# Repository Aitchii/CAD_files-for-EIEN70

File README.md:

# CAD_files-for-EIEN70
CAD files for Mechatronics project EIEN70  
Contrains three different Kicad models:   
Första-projekt = LED_ring without PCB design  
LED_ring  
IR_sensor

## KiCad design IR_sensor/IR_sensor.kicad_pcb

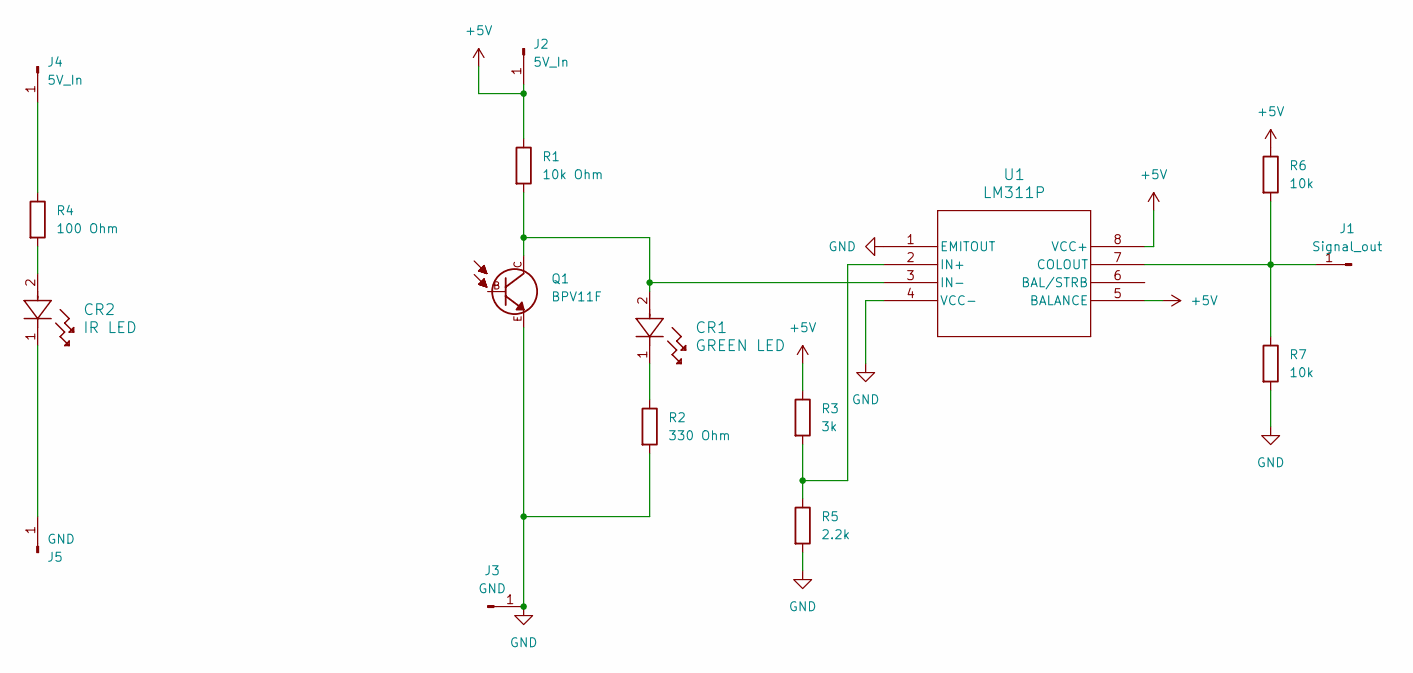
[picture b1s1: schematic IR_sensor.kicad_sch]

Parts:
CR1: GREEN LED; TLL_Series_LED_GR
CR2: IR LED; LED_D5.0mm_IRGrey
J1: Signal_out; PinHeader_1x01_P2.54mm_Vertical
J2, J4: 5V_In; PinHeader_1x01_P2.54mm_Vertical
J3, J5: GND; PinHeader_1x01_P2.54mm_Vertical
Q1: BPV11F; Phototransistor
R1: 10k Ohm; R_Axial_DIN0204_L3.6mm_D1.6mm_P5.08mm_Horizontal
R2: 330 Ohm; R_Axial_DIN0204_L3.6mm_D1.6mm_P5.08mm_Horizontal
R3: 3k; R_Axial_DIN0204_L3.6mm_D1.6mm_P5.08mm_Horizontal
R4: 100 Ohm; R_Axial_DIN0204_L3.6mm_D1.6mm_P5.08mm_Horizontal
R5: 2.2k; R_Axial_DIN0204_L3.6mm_D1.6mm_P5.08mm_Horizontal
R6, R7: 10k; R_Axial_DIN0204_L3.6mm_D1.6mm_P5.08mm_Horizontal
U1: LM311P; Voltage_comparator

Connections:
+5V: J2.1, R1.1, R3.1, R6.1, U1.5 (BALANCE), U1.8 (VCC+)
GND: J3.1, Q1.E, R2.2, R5.2, R7.2, U1.1 (EMITOUT), U1.4 (VCC-)
unnamed: CR1.1, R2.1
unnamed: CR2.2, R4.2
unnamed: J1.1, R6.2, R7.1, U1.7 (COLOUT)
unnamed: J4.1, R4.1
unnamed: CR2.1, J5.1
unnamed: R3.2, R5.1, U1.2 (IN+)
unnamed: CR1.2, Q1.C, R1.2, U1.3 (IN-)

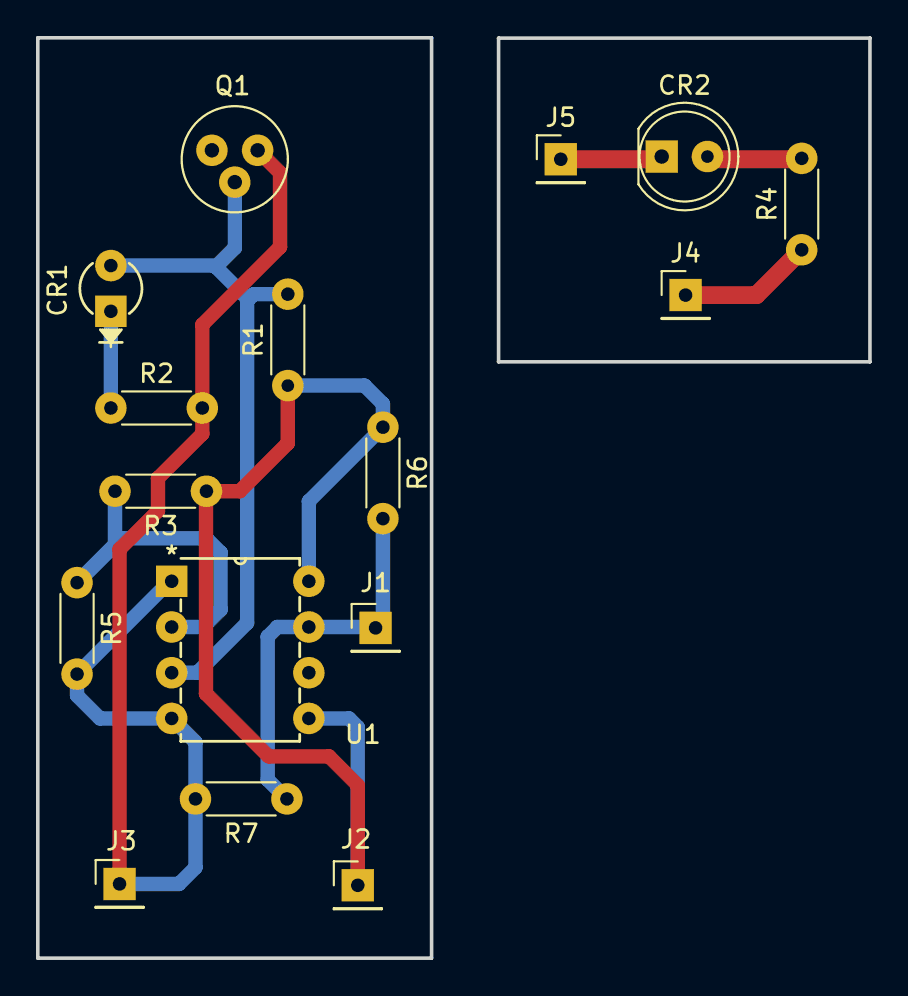
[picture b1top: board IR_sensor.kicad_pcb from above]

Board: 2 copper layers, 46.2 x 51.1 mm, 16 parts (0 on the bottom side), 9 nets.

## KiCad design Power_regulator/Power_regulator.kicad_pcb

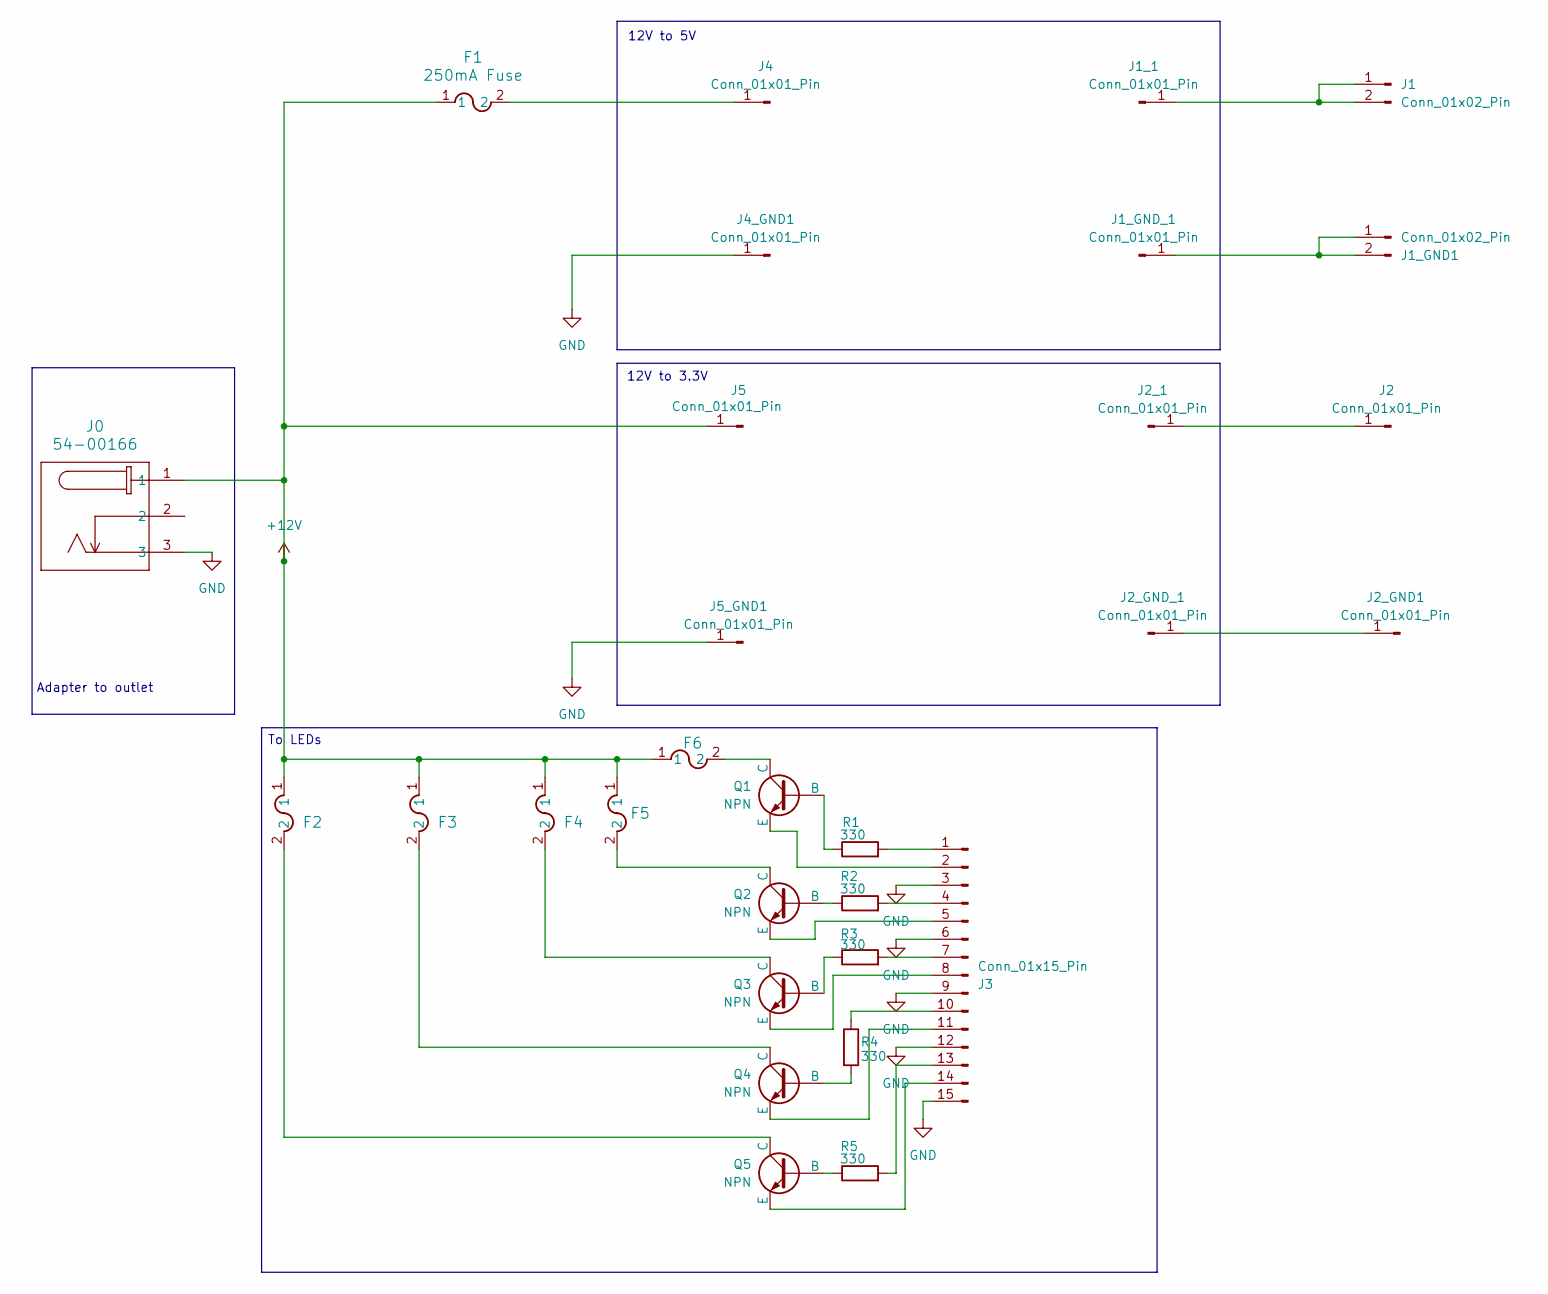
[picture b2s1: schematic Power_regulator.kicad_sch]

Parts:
F1: 250mA Fuse; FUS_LITTELFUSE_370_LTF_250mA
F2, F3, F4, F5, F6: 100mA Fuse; FUS_LITTELFUSE_396_LTF_100mA
J0: 54-00166; CONN3_54-00166_TEN
J1, J1_GND1: Conn_01x02_Pin; PinHeader_1x02_P2.54mm_Vertical
J1_1, J1_GND_1, J2, J2_1, J2_GND1, J2_GND_1, J4, J4_GND1, J5, J5_GND1: Conn_01x01_Pin; PinHeader_1x01_P2.54mm_Vertical
J3: Conn_01x15_Pin; PinHeader_1x15_P2.54mm_Vertical
Q1, Q2, Q3, Q4, Q5: NPN; NPN_transistor
R1, R2, R3, R4, R5: 330; R_Axial_DIN0204_L3.6mm_D1.6mm_P7.62mm_Horizontal

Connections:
+12V: F1.1, F2.1, F3.1, F4.1, F5.1, F6.1, J0.1, J5.1
GND: J0.3, J3.3, J3.6, J3.9, J3.12, J3.15, J4_GND1.1, J5_GND1.1
unnamed: J1.1, J1.2, J1_1.1
unnamed: J1_GND1.1, J1_GND1.2, J1_GND_1.1
unnamed: J2.1, J2_1.1
unnamed: J2_GND1.1, J2_GND_1.1
unnamed: J3.1, R1.2
unnamed: J3.2, Q1.3 (E)
unnamed: J3.4, R2.2
unnamed: J3.5, Q2.3 (E)
unnamed: J3.7, R3.2
unnamed: J3.8, Q3.3 (E)
unnamed: J3.10, R4.1
unnamed: J3.11, Q4.3 (E)
unnamed: J3.13, R5.2
unnamed: J3.14, Q5.3 (E)
unnamed: F1.2, J4.1
unnamed: Q1.2 (B), R1.1
unnamed: F6.2, Q1.1 (C)
unnamed: Q2.2 (B), R2.1
unnamed: F5.2, Q2.1 (C)
unnamed: Q3.2 (B), R3.1
unnamed: F4.2, Q3.1 (C)
unnamed: Q4.2 (B), R4.2
unnamed: F3.2, Q4.1 (C)
unnamed: Q5.2 (B), R5.1
unnamed: F2.2, Q5.1 (C)

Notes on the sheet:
To LEDs
12V to 5V
12V to 3.3V
Adapter to outlet

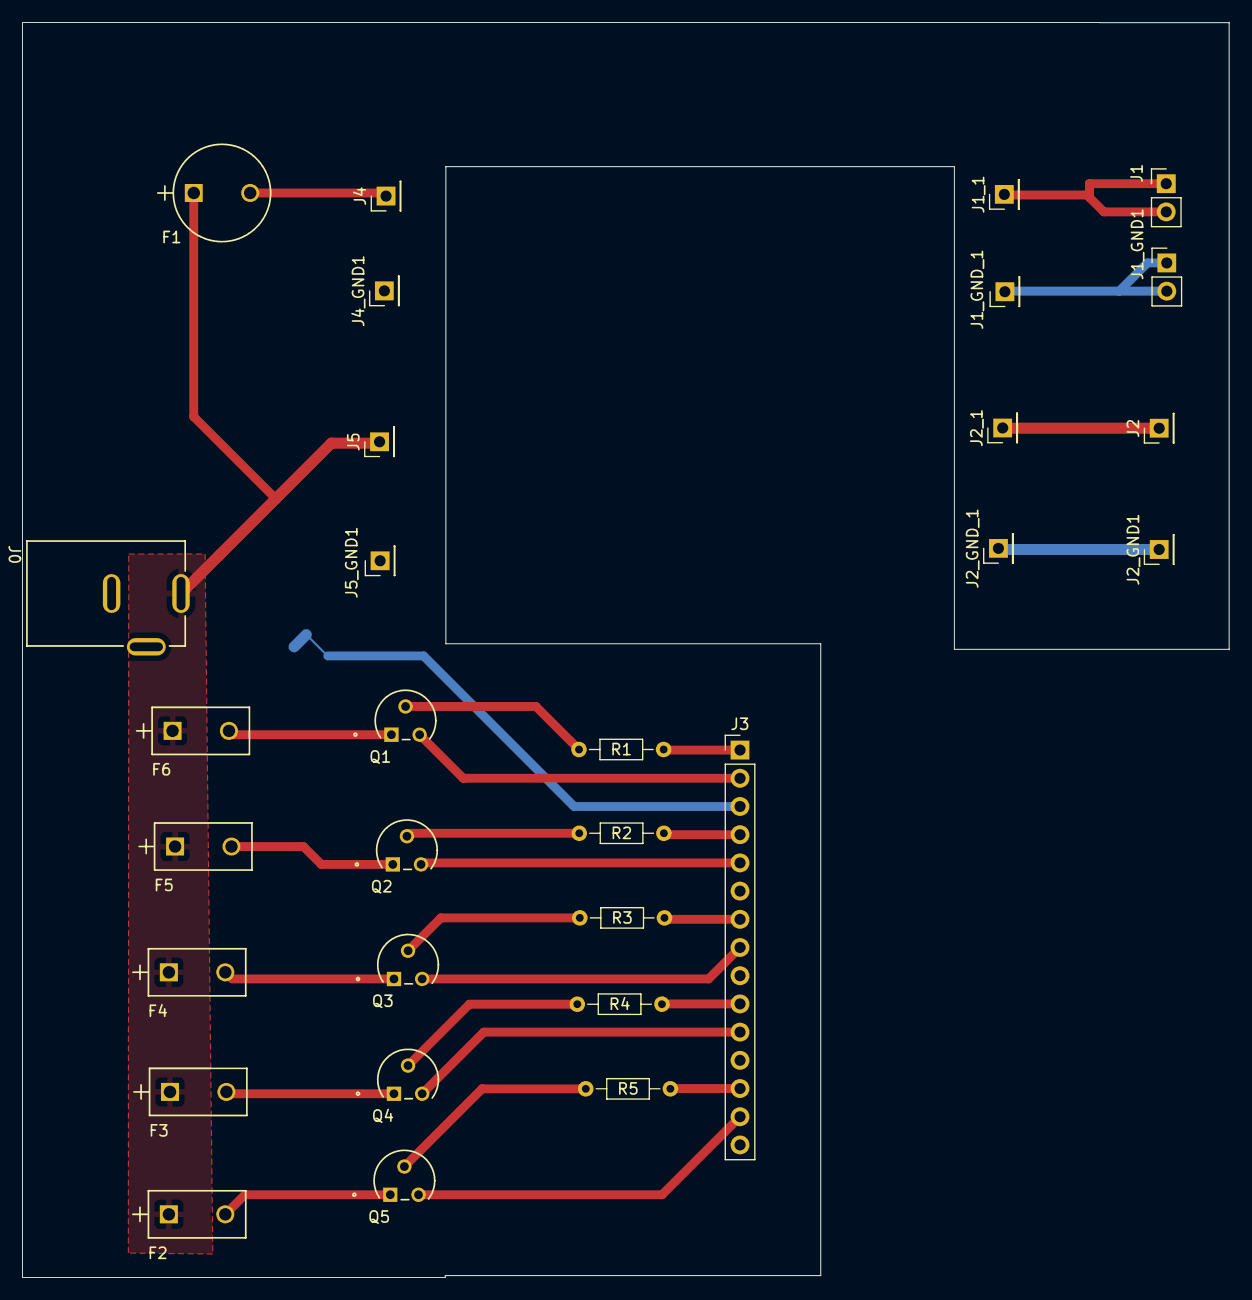
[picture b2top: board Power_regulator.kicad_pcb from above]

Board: 2 copper layers, 108.7 x 113.0 mm, 30 parts (0 on the bottom side), 27 nets.

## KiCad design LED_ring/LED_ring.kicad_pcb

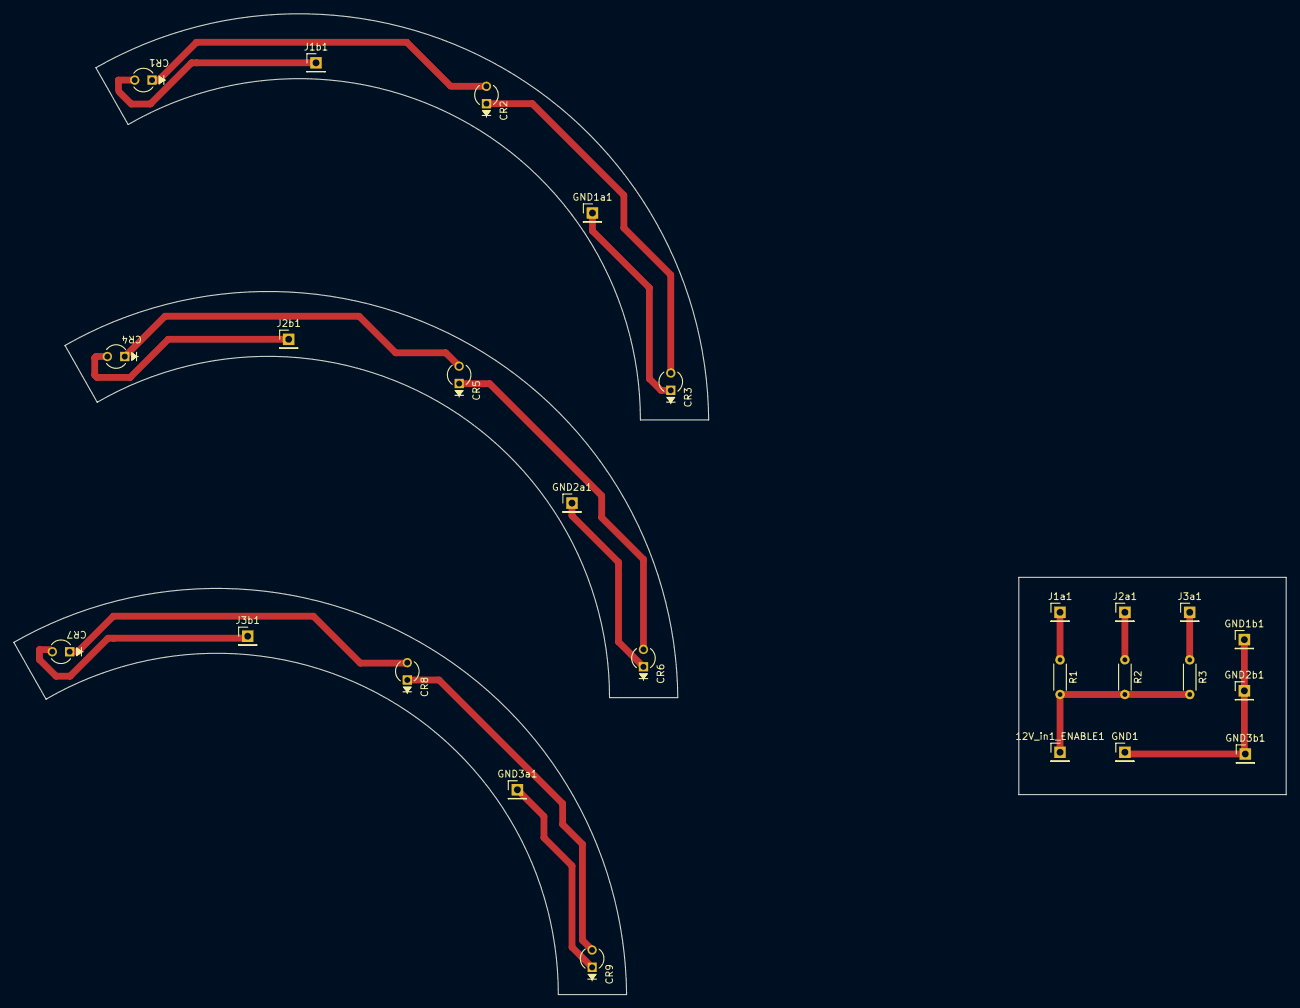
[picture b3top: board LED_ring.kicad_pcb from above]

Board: 2 copper layers, 186.4 x 143.7 mm, 26 parts (0 on the bottom side), 16 nets.

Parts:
12V_in1_ENABLE1: Conn_01x01_Pin; PinHeader_1x01_P2.54mm_Vertical
CR1, CR2, CR3, CR4, CR5, CR6, CR7, CR8, CR9: TLLG4401; TLL_Series_VIS
GND1, GND1a1, GND1b1, GND2a1, GND2b1, GND3a1, GND3b1: Conn_01x01_Pin; PinHeader_1x01_P2.54mm_Vertical
J1a1, J1b1, J2a1, J2b1, J3a1, J3b1: Conn_01x01_Pin; PinHeader_1x01_P2.54mm_Vertical
R1, R2, R3: 100; R_Axial_DIN0204_L3.6mm_D1.6mm_P5.08mm_Horizontal

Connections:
unnamed: 12V_in1_ENABLE1.1, R1.2, R2.2, R3.2
unnamed: CR1.1, CR2.2
unnamed: CR2.1, CR3.2
unnamed: CR4.1, CR5.2
unnamed: CR5.1, CR6.2
unnamed: CR7.1, CR8.2
unnamed: CR8.1, CR9.1, CR9.2, GND3a1.1
unnamed: GND1.1, GND1b1.1, GND2b1.1, GND3b1.1
unnamed: CR3.1, GND1a1.1
unnamed: CR6.1, GND2a1.1
unnamed: J1a1.1, R1.1
unnamed: CR1.2, J1b1.1
unnamed: J2a1.1, R2.1
unnamed: CR4.2, J2b1.1
unnamed: J3a1.1, R3.1
unnamed: CR7.2, J3b1.1

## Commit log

2025-02-26 Added folder of Kicad files
2025-02-26 Adding IR_sensor
2025-02-26 Adding LED_ring folder
2025-02-26 Added additional files needed
2025-02-26 Just new save from other computer
2025-02-26 Resolving merge issues
2025-02-26 Adding SYM files for components
2025-02-26 Fixed new symbols
2025-02-26 added schematic of IR_sensor
2025-02-27 Updated version
2025-02-27 Added new PCB design
2025-03-05 Begin development of power regulator
2025-03-05 New save of regulator files
2025-03-07 New save
2025-03-10 Started fxing the power_regulator
2025-03-23 Changed values on resistors
2025-03-31 New design for power regulation circuit
2025-04-01 Modified to fit with new spec
2025-04-01 Divided transmitter and reciever
2025-04-03 Finalized PCB design
2025-04-06 Finalized design for power regulator
2025-04-07 PCB done
2025-04-07 Added new component
2025-04-14 Generated output files for printing
2025-05-12 Changed pcb design, added voltage division on output
2025-05-15 Updated resistor values
2025-05-22 Took some screenshots, changed the transistors of the power regulator
